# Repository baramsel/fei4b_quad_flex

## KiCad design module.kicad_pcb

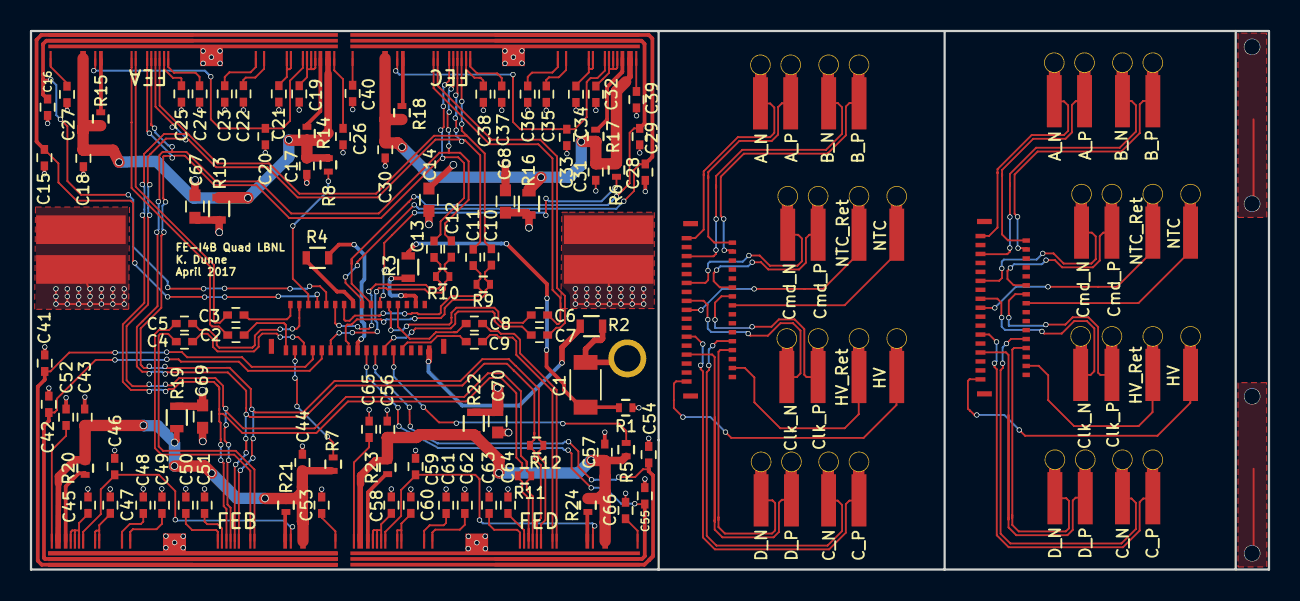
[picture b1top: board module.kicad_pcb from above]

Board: 2 copper layers, 82.9 x 36.1 mm, 137 parts (0 on the bottom side), 121 nets.

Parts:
C1: 1n; C_1206
C2, C3, C4, C5, C6, C7, C8, C9, C10, C11, C12, C13: 10n; C_0402
C14, C67, C68, C69, C70: 10u; C_0603
C15, C16, C17, C18, C19, C20, C21, C22, C23, C24, C25, C26, C27, C28, C29, C30, C31, C32, C33, C34, C35, C36, C37, C38, C39, C40, C41, C42, C43, C44, C45, C46, C47, C48, C49, C50, C51, C52, C53, C54, C55, C56, C57, C58, C59, C60, C61, C62, C63, C64, C65, C66: 2.2u; C_0402
FE1, FE2, FE3, FE3#2, FE4: FE-I4B; WirebondPads
J1, J2, J2#2: Conn; conn
R1, R14, R15, R17, R18, R20, R21, R23, R24: R_0402
R2, R3, R4: 10k; R_0603
R5, R6, R7, R8: 0; R_0402
R9, R10, R11, R12: 100; R_0402
R13, R16, R19, R22: 10m; R_0603
U1, U2: Solder_Pad; Power_Pad
U3: HV
U4, U4#2, U5, U5#2, U6, U6#2, U7, U7#2, U8, U8#2, U9, U9#2, U10, U10#2, U11, U11#2, U12, U12#2, U13, U13#2, U14, U14#2, U15, U15#2, U16, U16#2, U17, U17#2, U18, U18#2, U19, U19#2: term

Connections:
/Clk_N: C10.1, C10.2, FE1.88, FE2.88, FE3.88, FE4.88, J1.15, R9.1, R11.1
/Clk_P: C11.1, C11.2, FE1.89, FE2.89, FE3.89, FE4.89, J1.14, R9.2, R11.2
/Cmd_N: C12.1, C12.2, FE1.90, FE2.90, FE3.90, FE4.90, J1.11, R10.1, R12.1
/Cmd_P: C13.1, C13.2, FE1.91, FE2.91, FE3.91, FE4.91, J1.12, R10.2, R12.2
/DO_A_N: C2.1, J1.1
/DO_A_P: C3.1, J1.2
/DO_B_N: C4.1, J1.5
/DO_B_P: C5.1, J1.4
/DO_C_N: C6.1, J1.24
/DO_C_P: C7.1, J1.23
/DO_D_N: C8.1, J1.26
/DO_D_P: C9.1, J1.27
/FEA/DetBias_L: C26.1, FE1.B1
/FEA/DetBias_R: C27.1, FE1.B12
/FEA/GadcVref_P: C23.1, FE1.43
/FEA/Iref_out_P: C21.1, FE1.29, FE1.30
/FEA/RA1bar_P: C22.1, FE1.41
/FEA/RD1bar_P: C24.1, FE1.84
/FEA/RD2Bar_P: C25.1, FE1.85
/FEA/Vin: C14.1, C67.1, C68.1, C69.1, C70.1, R13.2, R16.2, R19.2, R22.2, U1.1, U1.2
/FEA/Vref1: C20.1, FE1.21, FE1.117
/FEA/Vref2: C19.1, FE1.15, FE1.19, FE1.B8
/FEA_N: C2.2, FE1.100
/FEA_P: C3.2, FE1.99
/FEB/DetBias_L: C52.1, FE3.B1
/FEB/DetBias_R: C53.1, FE3.B12
/FEB/GadcVref_P: C49.1, FE3.43
/FEB/Iref_out_P: C47.1, FE3.29, FE3.30
/FEB/RA1bar_P: C48.1, FE3.41
/FEB/RD1bar_P: C50.1, FE3.84
/FEB/RD2Bar_P: C51.1, FE3.85
/FEB/Vref1: C46.1, FE3.21, FE3.117
/FEB/Vref2: C45.1, FE3.15, FE3.19, FE3.B8
/FEB_N: C4.2, FE3.100
/FEB_P: C5.2, FE3.99
/FEC/DetBias_L: C39.1, FE2.B1
/FEC/DetBias_R: C40.1, FE2.B12
/FEC/GadcVref_P: C36.1, FE2.43
/FEC/Iref_out_P: C34.1, FE2.29, FE2.30
/FEC/RA1bar_P: C35.1, FE2.41
/FEC/RD1bar_P: C37.1, FE2.84
/FEC/RD2Bar_P: C38.1, FE2.85
/FEC/Vref1: C33.1, FE2.21, FE2.117
/FEC/Vref2: C32.1, FE2.15, FE2.19, FE2.B8
/FEC_N: C6.2, FE2.100
/FEC_P: C7.2, FE2.99
/FED/DetBias_L: C65.1, FE4.B1
/FED/DetBias_R: C66.1, FE4.B12
/FED/GadcVref_P: C62.1, FE4.43
/FED/Iref_out_P: C60.1, FE4.29, FE4.30
/FED/RA1bar_P: C61.1, FE4.41
/FED/RD1bar_P: C63.1, FE4.84
/FED/RD2Bar_P: C64.1, FE4.85
/FED/Vref1: C59.1, FE4.21, FE4.117
/FED/Vref2: C58.1, FE4.15, FE4.19, FE4.B8
/FED_N: C8.2, FE4.100
/FED_P: C9.2, FE4.99
/HV: J1.33, R2.1
/HV_Ret: J1.30, R3.1
/NTC: J1.16, R4.1
/NTC_Ret: J1.17, R4.2
/VDA_A: C16.1, FE1.B4, J1.10
/VDA_B: C42.1, FE3.B4, J1.9
/VDA_C: C29.1, FE2.B4, J1.20
/VDA_D: C55.1, FE4.B4, J1.19
/VDD_A: C15.1, FE1.120, J1.8
/VDD_B: C41.1, FE3.120, J1.7
/VDD_C: C28.1, FE2.120, J1.18
/VDD_D: C54.1, FE4.120, J1.21
/Vin_Sense_A: C17.1, C18.1, FE1.121, FE1.B3, R8.1, R13.1, R14.2, R15.1
/Vin_Sense_B: C43.1, C44.1, FE3.121, FE3.B3, R7.1, R19.1, R20.2, R21.1
/Vin_Sense_C: C30.1, C31.1, FE2.121, FE2.B3, R6.1, R16.1, R17.2, R18.1
/Vin_Sense_D: C56.1, C57.1, FE4.121, FE4.B3, R5.1, R22.1, R23.2, R24.1
/connect/Clk_N: J2.15, J2#2.15, U7.1, U7#2.1, U7#2.e
/connect/Clk_P: J2.14, J2#2.14, U13.1, U13#2.1, U13#2.e
/connect/Cmd_N: J2.11, J2#2.11, U6.1, U6#2.1, U6#2.e
/connect/Cmd_P: J2.12, J2#2.12, U12.1, U12#2.1, U12#2.e
/connect/DO_A_N: J2.1, J2#2.1, U4.1, U4#2.1, U4#2.e
/connect/DO_A_P: J2.2, J2#2.2, U10.1, U10#2.1, U10#2.e
/connect/DO_B_N: J2.5, J2#2.5, U5.1, U5#2.1, U5#2.e
/connect/DO_B_P: J2.4, J2#2.4, U11.1, U11#2.1, U11#2.e
/connect/DO_C_N: J2.24, J2#2.24, U14.1, U14#2.1, U14#2.e
/connect/DO_C_P: J2.23, J2#2.23, U8.1, U8#2.1, U8#2.e
/connect/DO_D_N: J2.26, J2#2.26, U15.1, U15#2.1, U15#2.e
/connect/DO_D_P: J2.27, J2#2.27, U9.1, U9#2.1, U9#2.e
/connect/HV: J2.33, J2#2.33, U16.1, U16#2.1, U16#2.e
/connect/HV_Ret: J2.30, J2#2.30, U17.1, U17#2.1, U17#2.e
/connect/NTC: J2.16, J2#2.16, U19.1, U19#2.1, U19#2.e
/connect/NTC_Ret: J2.17, J2#2.17, U18.1, U18#2.1, U18#2.e
GND: C14.2, C15.2, C16.2, C17.2, C18.2, C19.2, C20.2, C21.2, C22.2, C23.2, C24.2, C25.2, C26.2, C27.2, C28.2, C29.2, C30.2, C31.2, C32.2, C33.2, C34.2, C35.2, C36.2, C37.2, C38.2, C39.2, C40.2, C41.2, C42.2, C43.2, C44.2, C45.2, C46.2, C47.2, C48.2, C49.2, C50.2, C51.2, C52.2, C53.2, C54.2, C55.2, C56.2, C57.2, C58.2, C59.2, C60.2, C61.2, C62.2, C63.2, C64.2, C65.2, C66.2, C67.2, C68.2, C69.2, C70.2, FE1.B5, FE2.B5, FE3.B5, FE4.B5, R1.2, U2.1, U2.2
unnamed: C1.1, R1.1, R3.2
unnamed: C1.2, R2.2, U3.1
unnamed: FE1.116, R15.2
unnamed: FE1.B7, R14.1
unnamed: FE2.116, R18.2
unnamed: FE2.B7, R17.1
unnamed: FE3.116, R21.2
unnamed: FE3.B7, R20.1
unnamed: FE4.116, R24.2
unnamed: FE4.B7, R23.1
unnamed: J1.3, R7.2
unnamed: J1.6, R8.2
unnamed: J1.22, R6.2
unnamed: J1.25, R5.2
unnamed: J2.3, J2#2.3
unnamed: J2.6, J2#2.6
unnamed: J2.7, J2#2.7
unnamed: J2.8, J2#2.8
unnamed: J2.9, J2#2.9
unnamed: J2.10, J2#2.10
unnamed: J2.13, J2#2.13
unnamed: J2.18, J2#2.18
unnamed: J2.19, J2#2.19
unnamed: J2.20, J2#2.20
unnamed: J2.21, J2#2.21
unnamed: J2.22, J2#2.22
unnamed: J2.25, J2#2.25
unnamed: J2.28, J2#2.28
unnamed: J2.29, J2#2.29
unnamed: J2.31, J2#2.31
unnamed: J2.32, J2#2.32

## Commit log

2017-07-15 Add schematic and gerber files
2017-07-15 Edit decoupling cap values for V/I ref and Regulators
2017-07-15 Connect analog/digital shunt circuits
2017-08-18 Remove ground/vddd rail
